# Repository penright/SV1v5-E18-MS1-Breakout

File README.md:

# SV1v5-E18-MS1-Breakout (Un Tested)
This is to break out the SV1v5 and E18-MS1 CC2530 Modules so that you can use them on a breadboard.

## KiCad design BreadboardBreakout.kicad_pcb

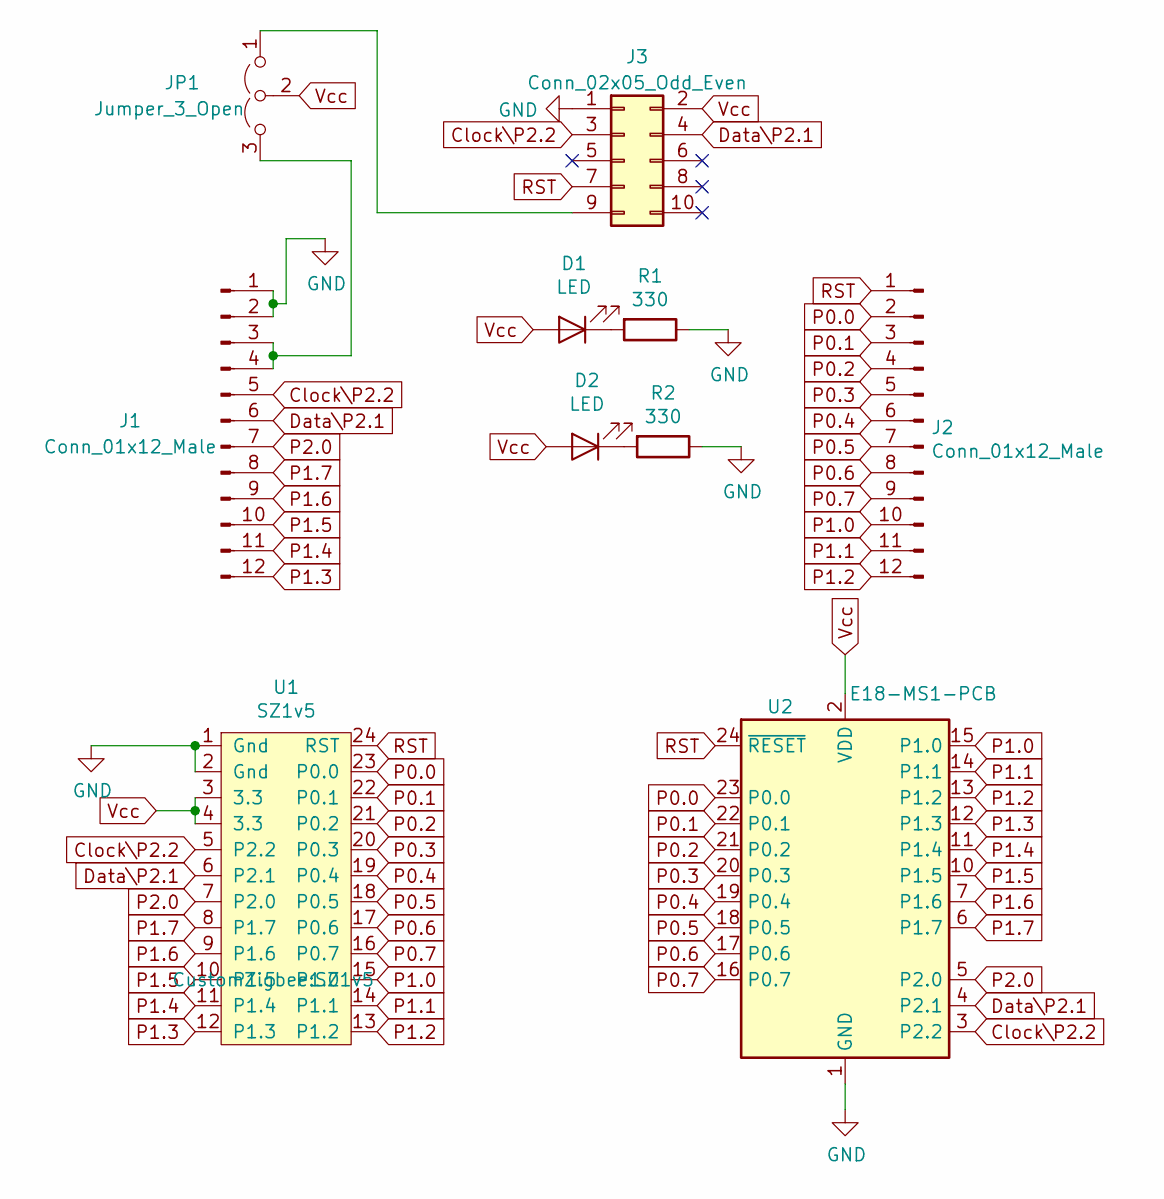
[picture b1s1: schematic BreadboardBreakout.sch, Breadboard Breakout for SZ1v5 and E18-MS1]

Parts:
D1, D2: LED; LED_1206_3216Metric_Pad1.42x1.75mm_HandSolder
J1, J2: Conn_01x12_Male; PinHeader_1x12_P2.54mm_Vertical
J3: Conn_02x05_Odd_Even; IDC-Header_2x05_P2.54mm_Vertical
JP1: Jumper_3_Open; PinHeader_1x03_P2.54mm_Vertical
R1, R2: 330; R_1206_3216Metric_Pad1.42x1.75mm_HandSolder
U1: SZ1v5
U2: E18-MS1-PCB

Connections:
Clock\P2.2: J1.5, J3.3, U1.5 (P2.2), U2.3 (P2.2)
Data\P2.1: J1.6, J3.4, U1.6 (P2.1), U2.4 (P2.1)
GND: J1.1, J1.2, J3.1, R1.1, R2.1, U1.1 (Gnd), U1.2 (Gnd), U2.1 (GND)
unnamed: D1.1 (K), R1.2
unnamed: D2.1 (K), R2.2
unnamed: J1.3, J1.4, JP1.3 (B)
unnamed: J3.9, JP1.1 (A)
P0.0: J2.2, U1.23 (P0.0), U2.23 (P0.0)
P0.1: J2.3, U1.22 (P0.1), U2.22 (P0.1)
P0.2: J2.4, U1.21 (P0.2), U2.21 (P0.2)
P0.3: J2.5, U1.20 (P0.3), U2.20 (P0.3)
P0.4: J2.6, U1.19 (P0.4), U2.19 (P0.4)
P0.5: J2.7, U1.18 (P0.5), U2.18 (P0.5)
P0.6: J2.8, U1.17 (P0.6), U2.17 (P0.6)
P0.7: J2.9, U1.16 (P0.7), U2.16 (P0.7)
P1.0: J2.10, U1.15 (P1.0), U2.15 (P1.0)
P1.1: J2.11, U1.14 (P1.1), U2.14 (P1.1)
P1.2: J2.12, U1.13 (P1.2), U2.13 (P1.2)
P1.3: J1.12, U1.12 (P1.3), U2.12 (P1.3)
P1.4: J1.11, U1.11 (P1.4), U2.11 (P1.4)
P1.5: J1.10, U1.10 (P1.5), U2.10 (P1.5)
P1.6: J1.9, U1.9 (P1.6), U2.7 (P1.6)
P1.7: J1.8, U1.8 (P1.7), U2.6 (P1.7)
P2.0: J1.7, U1.7 (P2.0), U2.5 (P2.0)
RST: J2.1, J3.7, U1.24 (RST), U2.24 (~RESET)
Vcc: D1.2 (A), D2.2 (A), J3.2, JP1.2 (C), U1.3 (3.3), U1.4 (3.3), U2.2 (VDD)

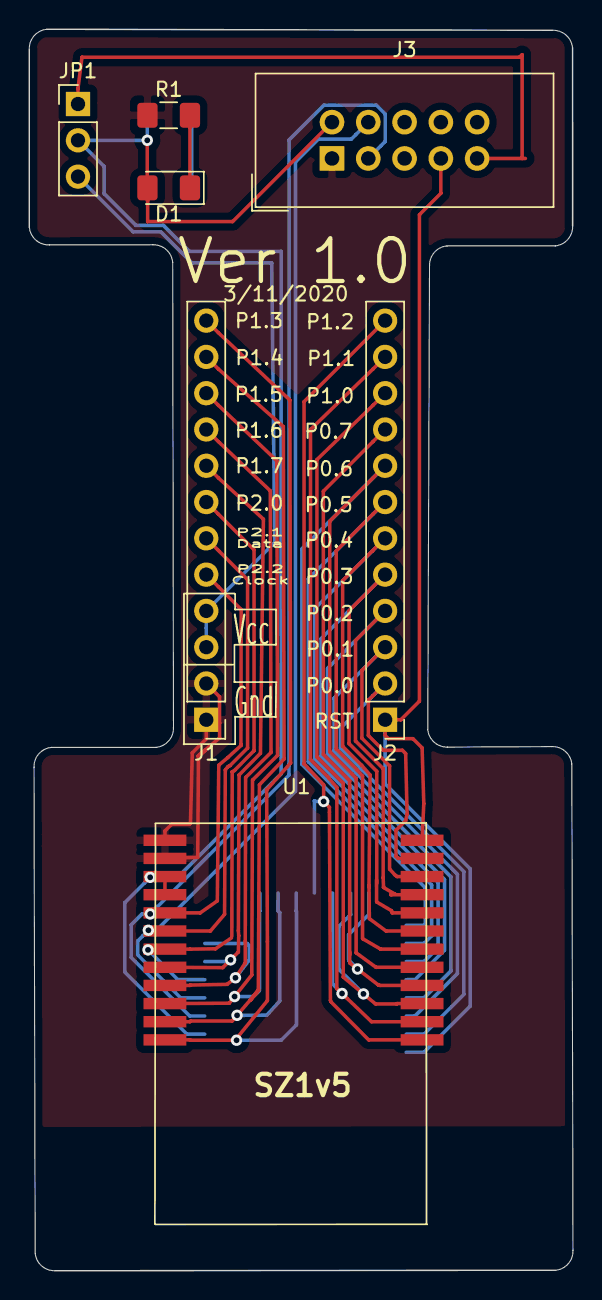
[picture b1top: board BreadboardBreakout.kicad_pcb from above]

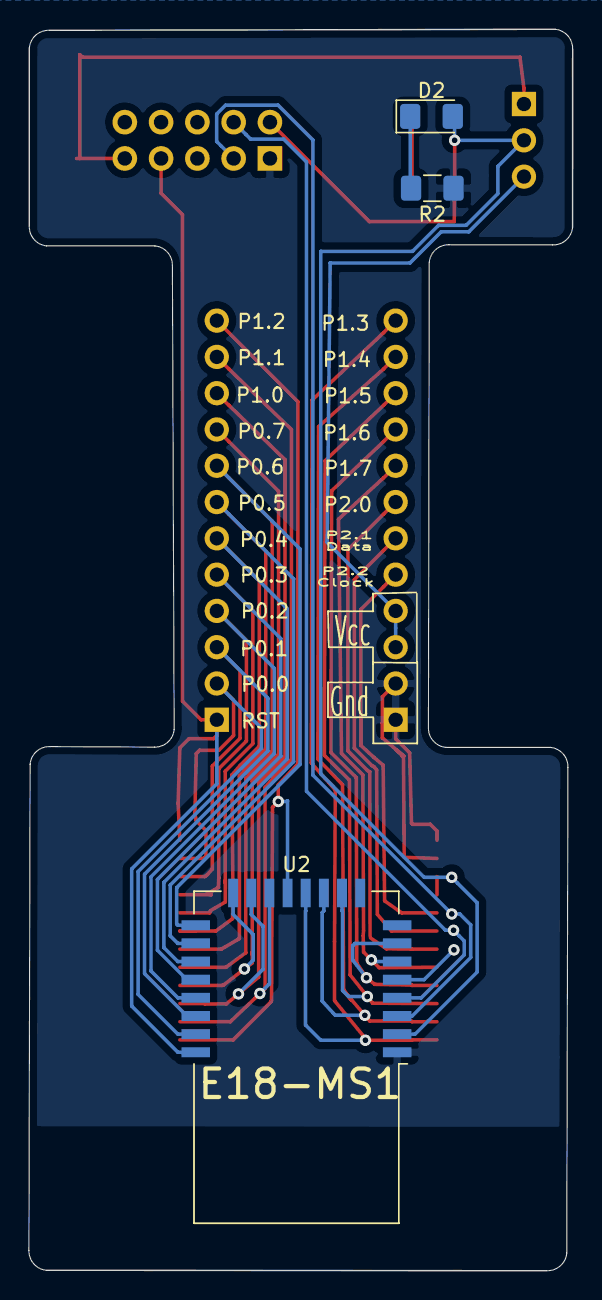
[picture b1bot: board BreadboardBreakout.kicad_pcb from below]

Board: 2 copper layers, 38.0 x 86.9 mm, 10 parts (3 on the bottom side), 26 nets.

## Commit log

2020-03-11 init
